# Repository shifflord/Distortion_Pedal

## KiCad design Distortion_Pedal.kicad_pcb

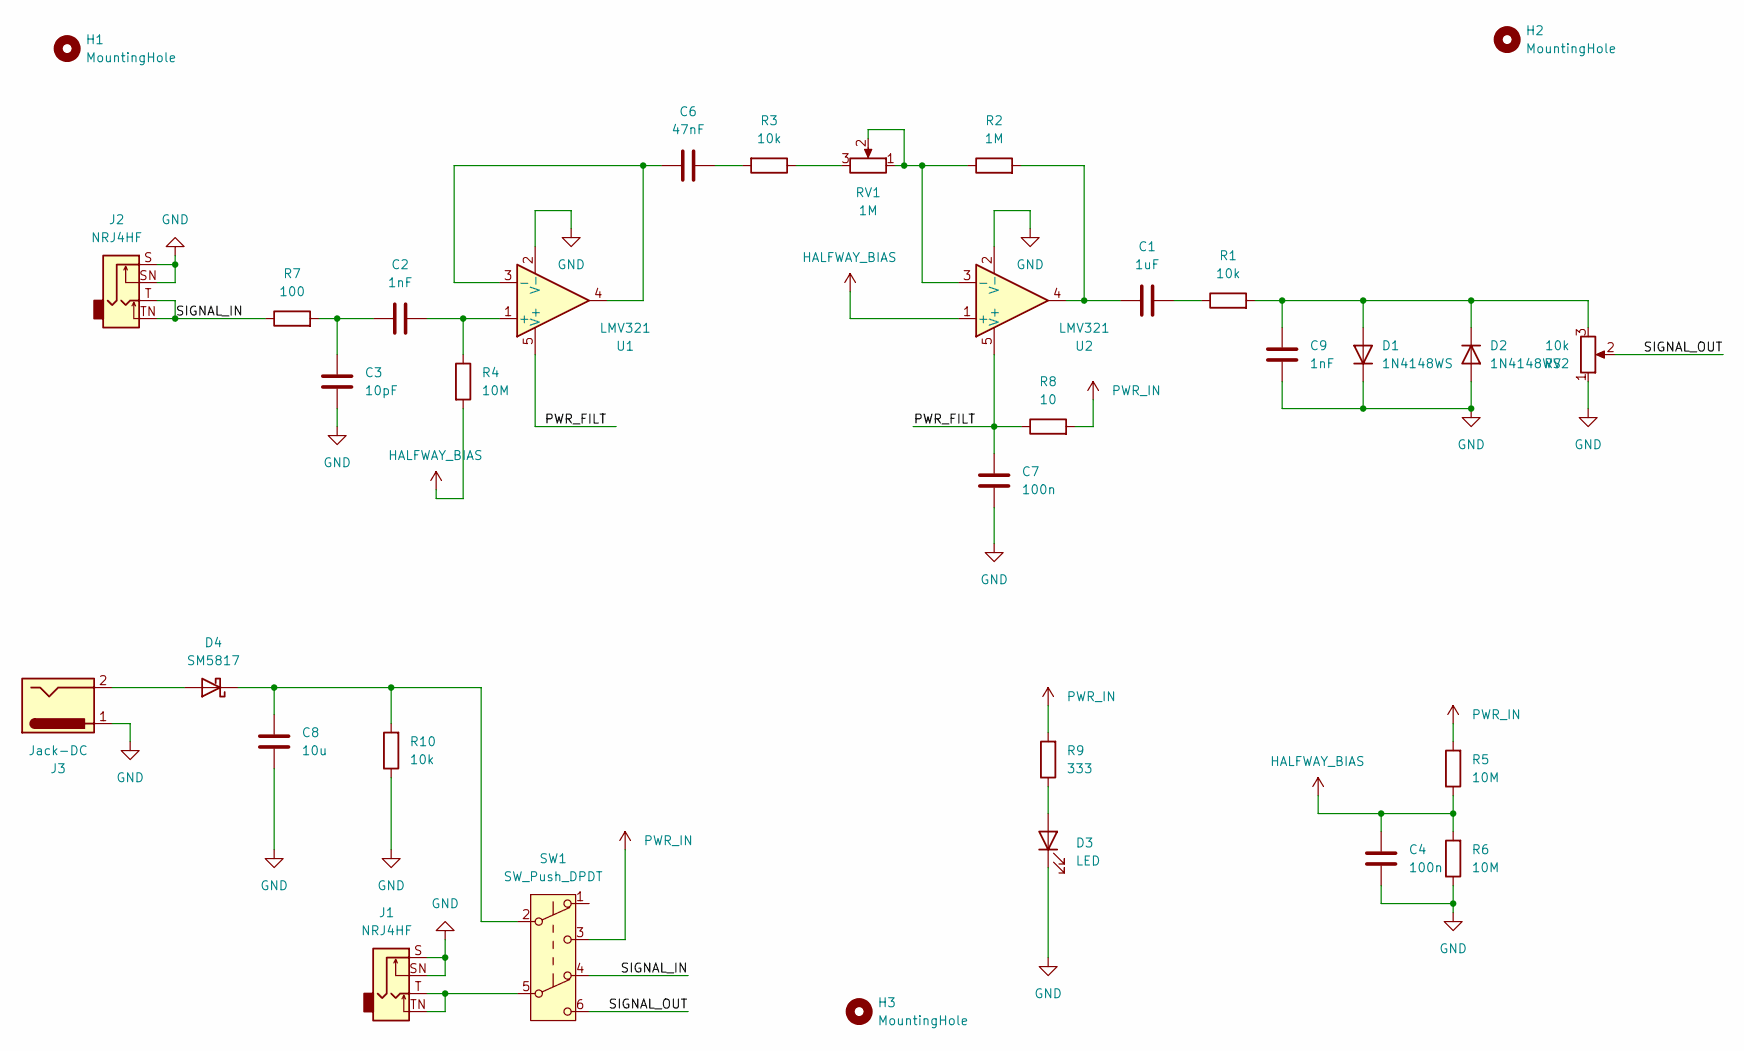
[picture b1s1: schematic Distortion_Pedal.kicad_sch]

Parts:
C1: 1uF; C_1206_3216Metric
C2, C9: 1nF; C_1206_3216Metric
C3: 10pF; C_1206_3216Metric
C4, C7: 100n; C_1206_3216Metric
C6: 47nF; C_1206_3216Metric
C8: 10u; C_1206_3216Metric
D1, D2: 1N4148WS; D_SOD-323
D3: LED; LED_1206_3216Metric
D4: SM5817; D_SOD-123
H1, H2, H3: MountingHole; MountingHole_2.2mm_M2
J1, J2: NRJ4HF; Jack_6.35mm_Neutrik_NRJ4HF_Horizontal
J3: Jack-DC; CONN3_54-00166_TEN
R1, R3, R10: 10k; R_1206_3216Metric
R2: 1M; R_1206_3216Metric
R4, R5, R6: 10M; R_1206_3216Metric
R7: 100; R_1206_3216Metric
R8: 10; R_1206_3216Metric
R9: 333; R_1206_3216Metric
RV1: 1M; TRIM_PT01-D120K2-B103
RV2: 10k; TRIM_PT01-D120K2-B103
SW1: SW_Push_DPDT; SW_TL2201EEYA_EWI
U1, U2: LMV321; SOT-23-5

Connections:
/PWR_FILT: C7.1, R8.1, U1.5 (V+), U2.5 (V+)
/SIGNAL_IN: J2.T, J2.TN, R7.1, SW1.4 (A)
/SIGNAL_OUT: RV2.2, SW1.6 (C)
GND: C3.1, C4.1, C7.2, C8.1, C9.1, D1.1 (K), D2.2 (A), D3.1 (K), J1.S, J1.SN, J2.S, J2.SN, J3.1, R6.1, R10.1, RV2.1, U1.2 (V-), U2.2 (V-)
HALFWAY_BIAS: C4.2, R4.2, R5.1, R6.2, U2.1 (+)
unnamed: C1.1, R2.2, U2.4
unnamed: C1.2, R1.1
unnamed: C2.1, C3.2, R7.2
unnamed: C6.2, R3.2
unnamed: C9.2, D1.2 (A), D2.1 (K), R1.2, RV2.3
unnamed: D3.2 (A), R9.1
unnamed: D4.2 (A), J3.2
unnamed: C8.2, D4.1 (K), R10.2, SW1.2 (B)
unnamed: J1.T, J1.TN, SW1.5 (B)
unnamed: R3.1, RV1.3
unnamed: C2.2, R4.1, U1.1 (+)
unnamed: C6.1, U1.3 (-), U1.4
unnamed: R2.1, RV1.1, RV1.2, U2.3 (-)
PWR_IN: R5.2, R8.2, R9.2, SW1.3 (C)

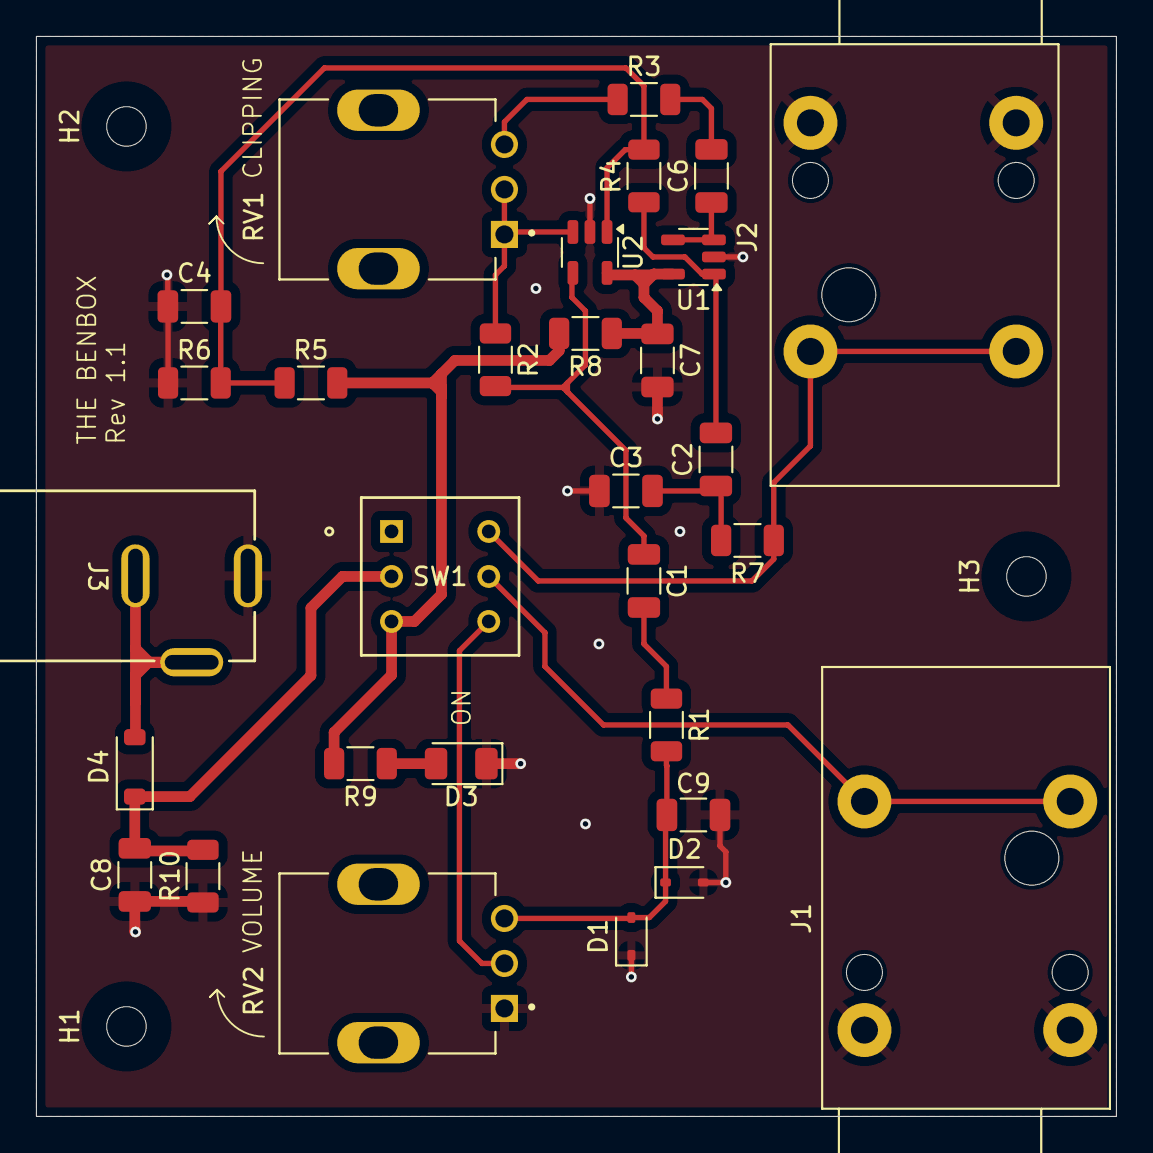
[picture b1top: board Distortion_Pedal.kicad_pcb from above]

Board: 2 copper layers, 60.0 x 60.0 mm, 33 parts (0 on the bottom side), 19 nets.
